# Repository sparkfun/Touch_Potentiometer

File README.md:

SparkFun Touch_Potentiometer
===================

[*SparkFun Touch Potentiometer (PRT-13144)*](https://www.sparkfun.com/products/13144)

The Touch Potentiometer is a collaboration between DanJulioDesigns and SparkFun Electronics. The Touch Pot allows you to easily integrate a slide potentiometer into any project that requires such an interface, such as the volume control on a stereo. 

Repository Contents
-------------------

* **/Documentation** - Data sheets, additional product information
* **/Hardware** - Eagle design files (.brd, .sch)
* **/Production** - Production panel files (.brd)

Documentation
--------------
* **[Hookup Guide](https://learn.sparkfun.com/tutorials/touch-potentiometer-hookup-guide)** - Basic hookup guide for the SparkFun Touch Potentiometer.
* **[SparkFun Fritzing repo](https://github.com/sparkfun/Fritzing_Parts)** - Fritzing diagrams for SparkFun products.
* **[SparkFun 3D Model repo](https://github.com/sparkfun/3D_Models)** - 3D models of SparkFun products. 

Product Versions
----------------
* [*SEN-13144*](https://www.sparkfun.com/products/13144)

Version History
---------------

* [V_1.0.0](https://github.com/sparkfun/SparkFun_BME280_Breakout_Board/tree/V_1.0.0) - Public release.

License Information
-------------------

This product is _**open source**_! 

Please review the LICENSE.md file for license information. 

If you have any questions or concerns on licensing, please contact techsupport@sparkfun.com.

Distributed as-is; no warranty is given.

- Your friends at SparkFun.

_<COLLABORATION CREDIT>_

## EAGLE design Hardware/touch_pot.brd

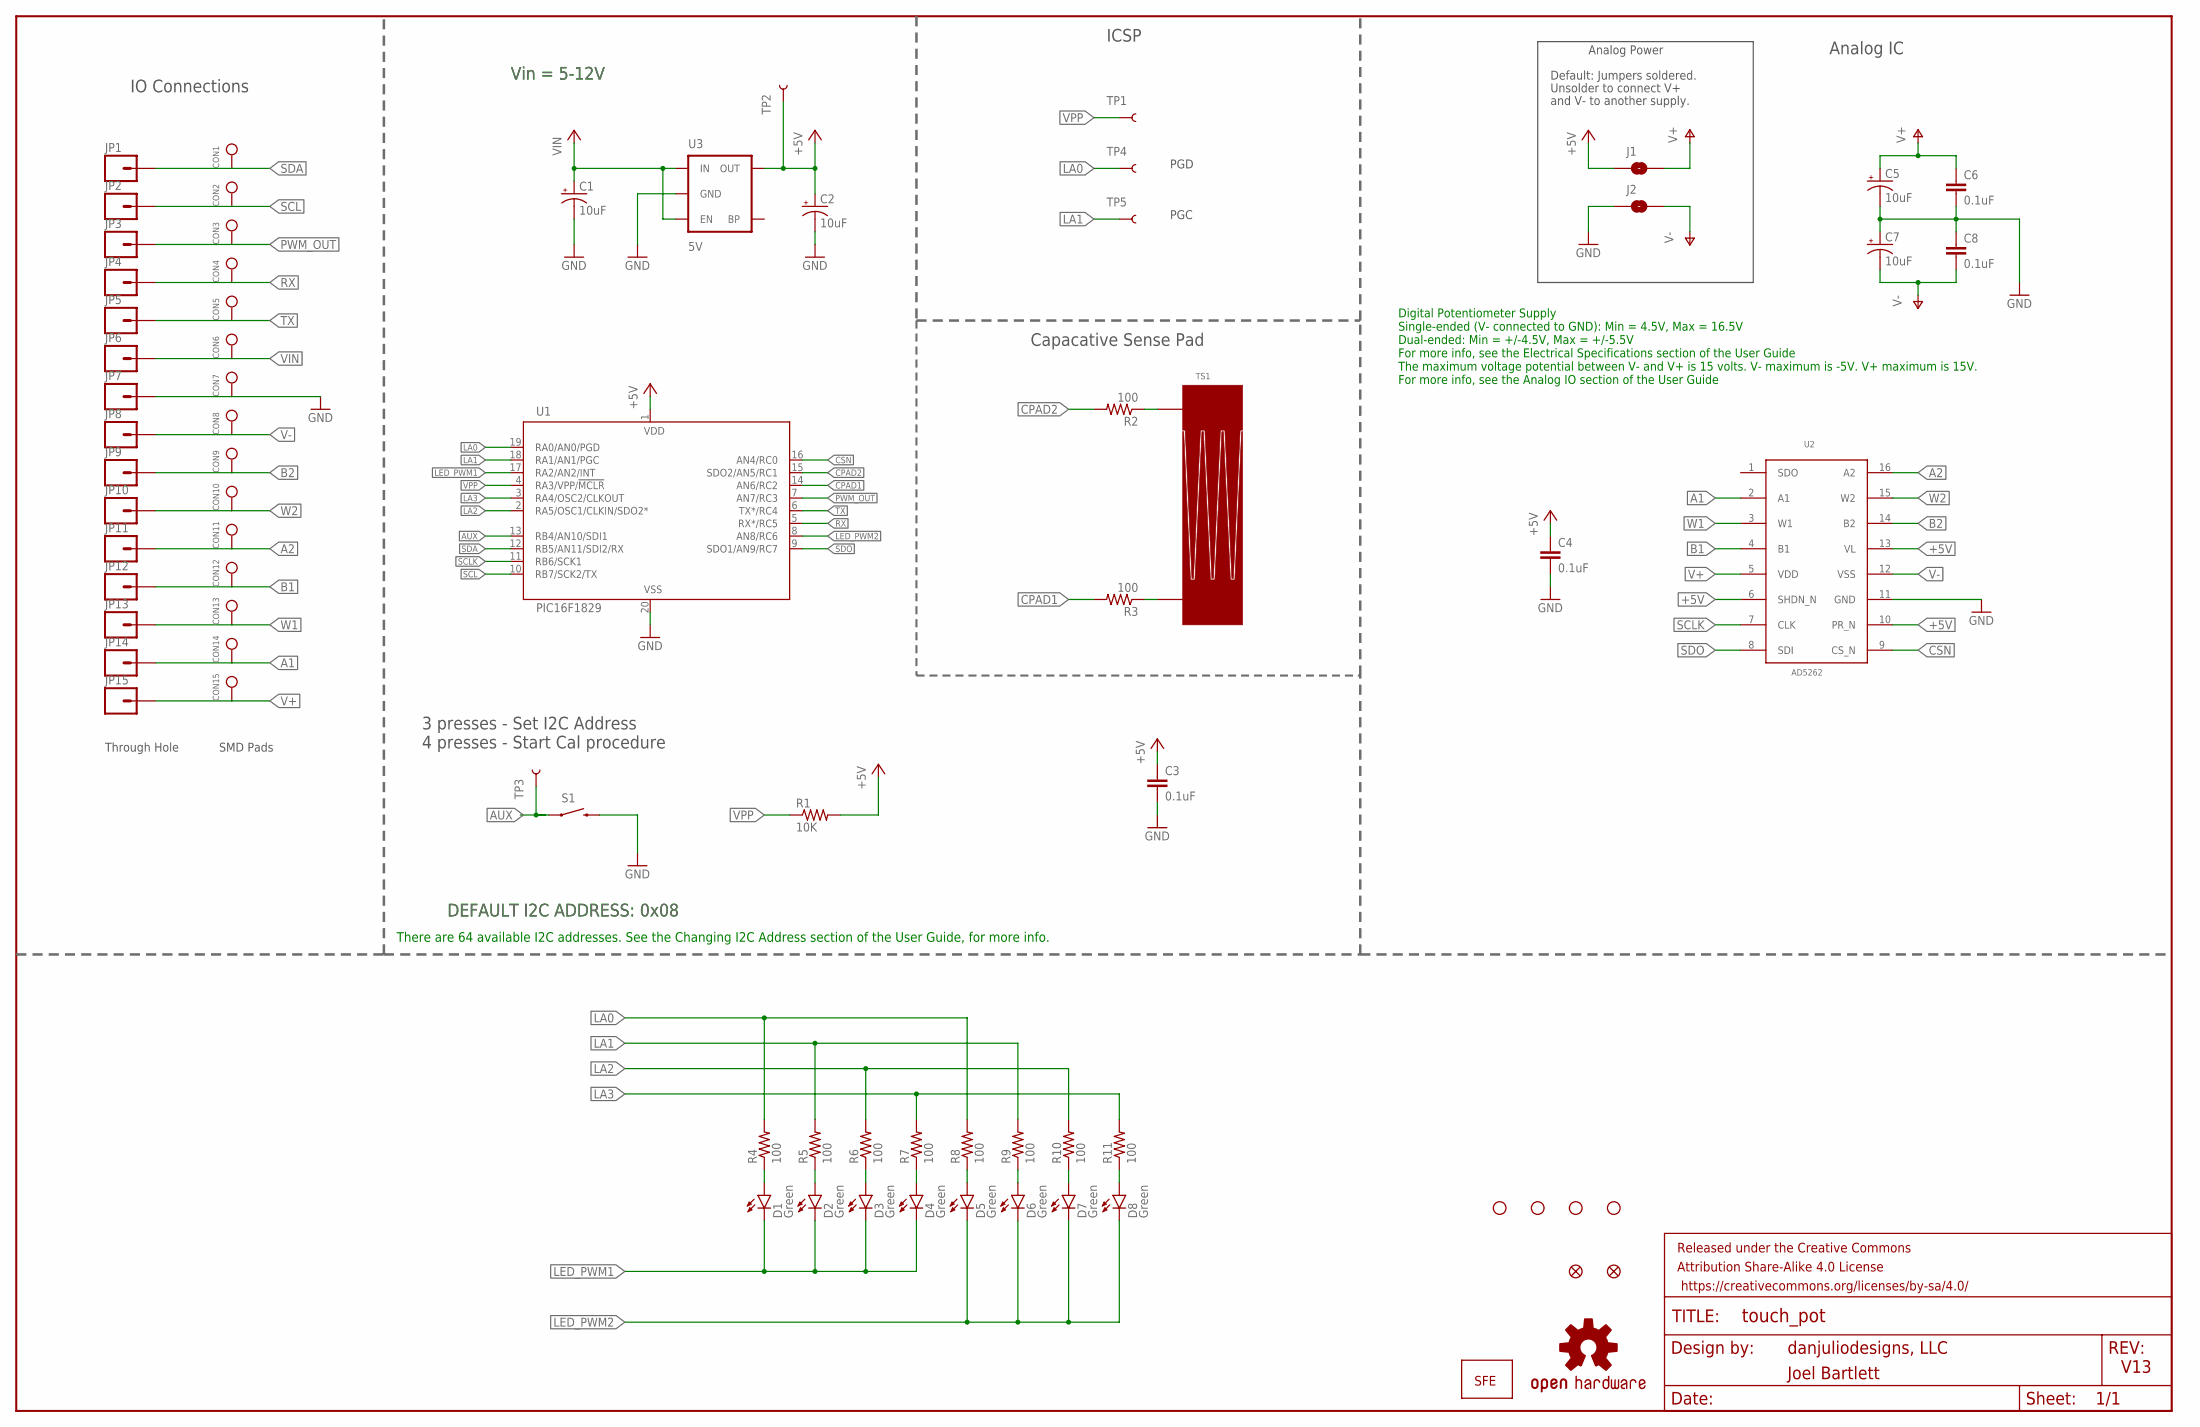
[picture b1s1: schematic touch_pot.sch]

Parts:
C1, C2, C5, C7: 10uF; EIA3216
C3, C4, C6, C8: 0.1uF; 0603-CAP
CON1, CON2, CON3, CON4, CON5, CON6, CON7, CON8, CON9, CON10, CON11, CON12, CON13, CON14, CON15: SINGLE_PADSMD; 2MM_SMD_PAD
D1, D2, D3, D4, D5, D6, D7, D8: Green; LED-1206-BOTTOM
FID1, FID2: FIDUCIAL1X2; FIDUCIAL-1X2
FRAME3: FRAME-LEDGER; CREATIVE_COMMONS
J1, J2: SJCLOSED; SJ_2S
JP1, JP2, JP3, JP4, JP5, JP6, JP7, JP8, JP9, JP10, JP11, JP12, JP13, JP14, JP15: M01SMDNS; 1X01NS
R1: 10K; 0603-RES
R2, R3, R4, R5, R6, R7, R8, R9, R10, R11: 100; 0603-RES
S1: SWITCH-MOMENTARY-2SMD; TACTILE-SWITCH-SMD
STANDOFF1, STANDOFF2, STANDOFF3, STANDOFF4: STAND-OFFTIGHT; STAND-OFF-TIGHT
TP1, TP2, TP3, TP4, TP5: TEST-POINT3X4; PAD.03X.04
TS1: 2CH_LINEAR_TOUCH; 2CH_48MM_LINEAR_TOUCH
U1: PIC16F1829; SSOP20
U2: AD5262; SSOP16
U3: 5V; SOT23-5
U$4: OSHW-LOGOM; OSHW-LOGO-M
U$5: SFE_LOGO_NAME_WEB; SFE-NEW-WEBLOGO

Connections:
+5V: C2.A (+), C3.1, C4.1, J1.1, R1.2, TP2.P$1, U1.1 (VDD), U2.6 (SHDN_N), U2.10 (PR_N), U2.13 (VL), U3.5 (OUT)
A1: CON14.P$1, JP14.1, U2.2 (A1)
A2: CON11.P$1, JP11.1, U2.16 (A2)
AUX: S1.1, TP3.P$1, U1.13 (RB4/AN10/SDI1)
B1: CON12.P$1, JP12.1, U2.4 (B1)
B2: CON9.P$1, JP9.1, U2.14 (B2)
CPAD1: R3.2, U1.14 (AN6/RC2)
CPAD2: R2.2, U1.15 (SDO2/AN5/RC1)
CSN: U1.16 (AN4/RC0), U2.9 (CS_N)
GND: C1.C (-), C2.C (-), C3.2, C4.2, C5.C (-), C6.2, C7.A (+), C8.1, CON7.P$1, J2.1, JP7.1, S1.3 (2), U1.20 (VSS), U2.11 (GND), U3.2 (GND)
LA0: R4.2, R8.2, TP4.P$1, U1.19 (RA0/AN0/PGD)
LA1: R5.2, R9.2, TP5.P$1, U1.18 (RA1/AN1/PGC)
LA2: R6.2, R10.2, U1.2 (RA5/OSC1/CLKIN/SDO2*)
LA3: R7.2, R11.2, U1.3 (RA4/OSC2/CLKOUT)
LED_PWM1: D1.C, D2.C, D3.C, D4.C, U1.17 (RA2/AN2/INT)
LED_PWM2: D5.C, D6.C, D7.C, D8.C, U1.8 (AN8/RC6)
unnamed: D1.A, R4.1
unnamed: D2.A, R5.1
unnamed: D3.A, R6.1
unnamed: D4.A, R7.1
unnamed: D5.A, R8.1
unnamed: D6.A, R9.1
unnamed: D7.A, R10.1
unnamed: D8.A, R11.1
unnamed: R2.1, TS1.P$2
unnamed: R3.1, TS1.P$1
PWM_OUT: CON3.P$1, JP3.1, U1.7 (AN7/RC3)
RX: CON4.P$1, JP4.1, U1.5 (RX*/RC5)
SCL: CON2.P$1, JP2.1, U1.10 (RB7/SCK2/TX)
SCLK: U1.11 (RB6/SCK1), U2.7 (CLK)
SDA: CON1.P$1, JP1.1, U1.12 (RB5/AN11/SDI2/RX)
SDO: U1.9 (SDO1/AN9/RC7), U2.8 (SDI)
TX: CON5.P$1, JP5.1, U1.6 (TX*/RC4)
V+: C5.A (+), C6.1, CON15.P$1, J1.2, JP15.1, U2.5 (VDD)
V-: C7.C (-), C8.2, CON8.P$1, J2.2, JP8.1, U2.12 (VSS)
VIN: C1.A (+), CON6.P$1, JP6.1, U3.1 (IN), U3.3 (EN)
VPP: R1.1, TP1.P$1, U1.4 (RA3/VPP/!MCLR)
W1: CON13.P$1, JP13.1, U2.3 (W1)
W2: CON10.P$1, JP10.1, U2.15 (W2)

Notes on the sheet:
danjuliodesigns, LLC
V13
3 presses - Set I2C Address 4 presses - Start Cal procedure
IO Connections
ICSP
Analog Power
Default: Jumpers soldered.
PGD
PGC
Unsolder to connect V+
and V- to another supply.
Through Hole
SMD Pads
Joel Bartlett
Analog IC
Vin = 5-12V
DEFAULT I2C ADDRESS: 0x08
Digital Potentiometer Supply Single-ended (V- connected to GND): Min = 4.5V, Max = 16.5V Dual-ended: Min = +/-4.5V, Max = +/-5.5V For more info, see the Electrical Specifications section of the User Guide The maximum voltage potential between V- and V+ is 15 volts. V- maximum is -5V. V+ maximum is 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
Capacative Sense Pad
There are 64 available I2C addresses. See the Changing I2C Address section of the User Guide, for more info.

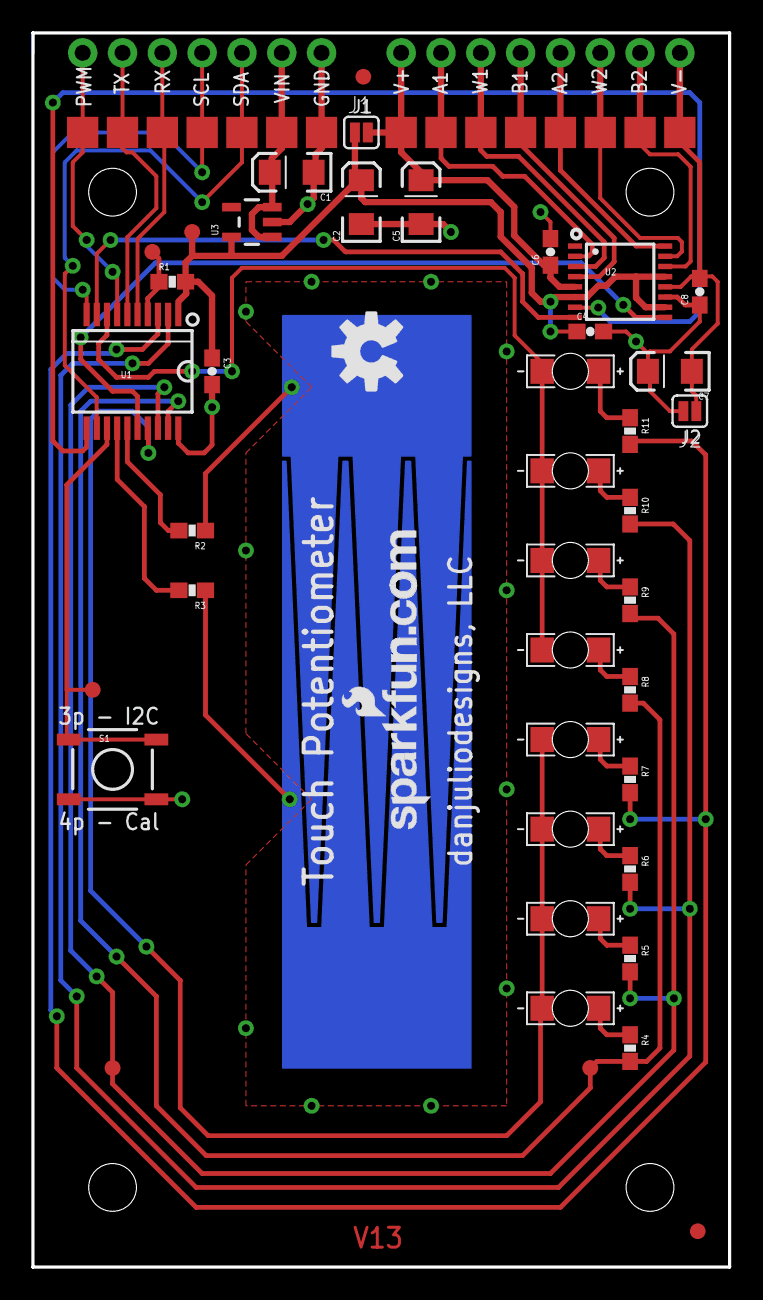
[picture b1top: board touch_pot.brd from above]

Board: 2 copper layers, 44.5 x 78.7 mm, 78 parts (1 on the bottom side), 39 nets.

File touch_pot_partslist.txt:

Partlist

Exported from touch_pot.sch at 6/7/14 7:36 PM

EAGLE Version 5.11.0 Copyright (c) 1988-2010 CadSoft

Part     Value           Device           Package               Library           Sheet

C1       10 uF           CAP_POL1206      EIA3216               SparkFun          1
C2       10 uF           CAP_POL1206      EIA3216               SparkFun          1
C3       0.1 uF          C-USSMT0603      C0603                 djd_eagle_library 1
C4       0.1 uF          C-USSMT0603      C0603                 djd_eagle_library 1
C5       10 uF           CAP_POL1206      EIA3216               SparkFun          1
C6       0.1 uF          C-USSMT0603      C0603                 djd_eagle_library 1
C7       10 uF           CAP_POL1206      EIA3216               SparkFun          1
C8       0.1 uF          C-USSMT0603      C0603                 djd_eagle_library 1
CON1     SINGLE_PADSMD   SINGLE_PADSMD    2MM_SMD_PAD           djd_eagle_library 1
CON2     SINGLE_PADSMD   SINGLE_PADSMD    2MM_SMD_PAD           djd_eagle_library 1
CON3     SINGLE_PADSMD   SINGLE_PADSMD    2MM_SMD_PAD           djd_eagle_library 1
CON4     SINGLE_PADSMD   SINGLE_PADSMD    2MM_SMD_PAD           djd_eagle_library 1
CON5     SINGLE_PADSMD   SINGLE_PADSMD    2MM_SMD_PAD           djd_eagle_library 1
CON6     SINGLE_PADSMD   SINGLE_PADSMD    2MM_SMD_PAD           djd_eagle_library 1
CON7     SINGLE_PADSMD   SINGLE_PADSMD    2MM_SMD_PAD           djd_eagle_library 1
CON8     SINGLE_PADSMD   SINGLE_PADSMD    2MM_SMD_PAD           djd_eagle_library 1
CON9     SINGLE_PADSMD   SINGLE_PADSMD    2MM_SMD_PAD           djd_eagle_library 1
CON10    SINGLE_PADSMD   SINGLE_PADSMD    2MM_SMD_PAD           djd_eagle_library 1
CON11    SINGLE_PADSMD   SINGLE_PADSMD    2MM_SMD_PAD           djd_eagle_library 1
CON12    SINGLE_PADSMD   SINGLE_PADSMD    2MM_SMD_PAD           djd_eagle_library 1
CON13    SINGLE_PADSMD   SINGLE_PADSMD    2MM_SMD_PAD           djd_eagle_library 1
CON14    SINGLE_PADSMD   SINGLE_PADSMD    2MM_SMD_PAD           djd_eagle_library 1
CON15    SINGLE_PADSMD   SINGLE_PADSMD    2MM_SMD_PAD           djd_eagle_library 1
CON16    SINGLE_PADSMD_R SINGLE_PADSMD_R  2MM_R_SMD_PAD         djd_eagle_library 1
CON17    SINGLE_PADSMD_R SINGLE_PADSMD_R  2MM_R_SMD_PAD         djd_eagle_library 1
CON18    SINGLE_PADSMD_R SINGLE_PADSMD_R  2MM_R_SMD_PAD         djd_eagle_library 1
D1       APTR3216SECK    LEDREV_32_16     REV_LED_32_16         djd_eagle_library 1
D2       APTR3216SECK    LEDREV_32_16     REV_LED_32_16         djd_eagle_library 1
D3       APTR3216SECK    LEDREV_32_16     REV_LED_32_16         djd_eagle_library 1
D4       APTR3216SECK    LEDREV_32_16     REV_LED_32_16         djd_eagle_library 1
D5       APTR3216SECK    LEDREV_32_16     REV_LED_32_16         djd_eagle_library 1
D6       APTR3216SECK    LEDREV_32_16     REV_LED_32_16         djd_eagle_library 1
D7       APTR3216SECK    LEDREV_32_16     REV_LED_32_16         djd_eagle_library 1
D8       APTR3216SECK    LEDREV_32_16     REV_LED_32_16         djd_eagle_library 1
J1                       SJCLOSED         SJ_2S                 djd_eagle_library 1
J2                       SJCLOSED         SJ_2S                 djd_eagle_library 1
JP1      M01SMDNS        M01SMDNS         1X01NS                SparkFun          1
JP2      M01SMDNS        M01SMDNS         1X01NS                SparkFun          1
JP3      M01SMDNS        M01SMDNS         1X01NS                SparkFun          1
JP4      M01SMDNS        M01SMDNS         1X01NS                SparkFun          1
JP5      M01SMDNS        M01SMDNS         1X01NS                SparkFun          1
JP6      M01SMDNS        M01SMDNS         1X01NS                SparkFun          1
JP7      M01SMDNS        M01SMDNS         1X01NS                SparkFun          1
JP8      M01SMDNS        M01SMDNS         1X01NS                SparkFun          1
JP9      M01SMDNS        M01SMDNS         1X01NS                SparkFun          1
JP10     M01SMDNS        M01SMDNS         1X01NS                SparkFun          1
JP11     M01SMDNS        M01SMDNS         1X01NS                SparkFun          1
JP12     M01SMDNS        M01SMDNS         1X01NS                SparkFun          1
JP13     M01SMDNS        M01SMDNS         1X01NS                SparkFun          1
JP14     M01SMDNS        M01SMDNS         1X01NS                SparkFun          1
JP15     M01SMDNS        M01SMDNS         1X01NS                SparkFun          1
PB1                      PB_TACT_4SMT     TACT_KPT_1187B        djd_eagle_library 1
R1       10 kohm         R-USSMT0603      R0603                 djd_eagle_library 1
R2       100 ohm         R-USSMT0603      R0603                 djd_eagle_library 1
R3       100 ohm         R-USSMT0603      R0603                 djd_eagle_library 1
R4       100 ohm         R-USSMT0603      R0603                 djd_eagle_library 1
R5       100 ohm         R-USSMT0603      R0603                 djd_eagle_library 1
R6       100 ohm         R-USSMT0603      R0603                 djd_eagle_library 1
R7       100 ohm         R-USSMT0603      R0603                 djd_eagle_library 1
R8       100 ohm         R-USSMT0603      R0603                 djd_eagle_library 1
R9       100 ohm         R-USSMT0603      R0603                 djd_eagle_library 1
R10      100 ohm         R-USSMT0603      R0603                 djd_eagle_library 1
R11      100 ohm         R-USSMT0603      R0603                 djd_eagle_library 1
TS1                      2CH_LINEAR_TOUCH 2CH_48MM_LINEAR_TOUCH djd_eagle_library 1
U1       PIC16F1829      PIC16F1829SSOP20 SSOP20                djd_eagle_library 1
U2       AD5262          AD6262TSSOP      SSOP16                djd_eagle_library 1
U3       V_REG_LDOSMD    V_REG_LDOSMD     SOT23-5               SparkFun          1

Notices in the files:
parts and their libraries:
SparkFun-Aesthetics: Licensing: Creative Commons ShareAlike 4.0 International - https://creativecommons.org/licenses/by-sa/4.0
SparkFun-Aesthetics: Released under the Creative Commons Attribution Share-Alike 4.0 License
SparkFun-Aesthetics: https://creativecommons.org/licenses/by-sa/4.0
